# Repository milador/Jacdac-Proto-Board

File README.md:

# Jacdac-Proto-Board
A protoboard for Jacdac plug-and-play microcontrollers

The goal of this project ia to create a custom protoboard with built-in support for Jacdac plug-and-play for microcontrollers. This custom protoboard allows the makers to prototype their ideas for Jacdac ecosystem.

## Features

  1. Jacdac Connectors x 2
  2. (5 x 12) connection pins x 1
  3. (1 x 12) Power rails x 1
  4. [Footprint for 3.5mm Stereo Jack (SJ1-3513)](https://www.digikey.com/en/products/detail/cui-devices/SJ1-3513/738683) x 2
  5. 3-Pin headers for Jacdac connectors x 2
  6. 1-Pin headers for 3.5mm Stereo Jack x 2

## Hardware

### Printed Circuit Board Design Files

All the EAGLE PCB design files and gerber files are available and can be downloaded using the following link:

<a href="https://github.com/milador/Jacdac-Proto-Board/tree/main/Hardware/PCB/Eagle">EAGLE Design files</a>

<a href="https://github.com/milador/Jacdac-Proto-Board/blob/main/Hardware/PCB/Gerbers/Jacdac_Proto_Board.zip">Gerber files</a>

### 3D Model of the Printed Circuit Board Design

The 3D Model of protoboard is available in STL format for 3D printing before PCB fabrication and can be downloaded using the following link:

<a href="https://github.com/milador/Jacdac-Proto-Board/blob/main/Hardware/3D-Model/Jacdac_Proto_Board_3D_Model.stl">STL file</a>

## Images

Top View:

Bottom View:

3D Model Top View:

3D Model  Bottom View:

Fabricated PCBs:

## License 

### MIT License

Copyright (c) 2021 Milador

Permission is hereby granted, free of charge, to any person obtaining a copy of this software and associated documentation files (the "Software"), to deal in the Software without restriction, including without limitation the rights to use, copy, modify, merge, publish, distribute, sublicense, and/or sell copies of the Software, and to permit persons to whom the Software is furnished to do so, subject to the following conditions:

The above copyright notice and this permission notice shall be included in all copies or substantial portions of the Software.

THE SOFTWARE IS PROVIDED "AS IS", WITHOUT WARRANTY OF ANY KIND, EXPRESS OR IMPLIED, INCLUDING BUT NOT LIMITED TO THE WARRANTIES OF MERCHANTABILITY, FITNESS FOR A PARTICULAR PURPOSE AND NONINFRINGEMENT. IN NO EVENT SHALL THE AUTHORS OR COPYRIGHT HOLDERS BE LIABLE FOR ANY CLAIM, DAMAGES OR OTHER LIABILITY, WHETHER IN AN ACTION OF CONTRACT, TORT OR OTHERWISE, ARISING FROM, OUT OF OR IN CONNECTION WITH THE SOFTWARE OR THE USE OR OTHER DEALINGS IN THE SOFTWARE.

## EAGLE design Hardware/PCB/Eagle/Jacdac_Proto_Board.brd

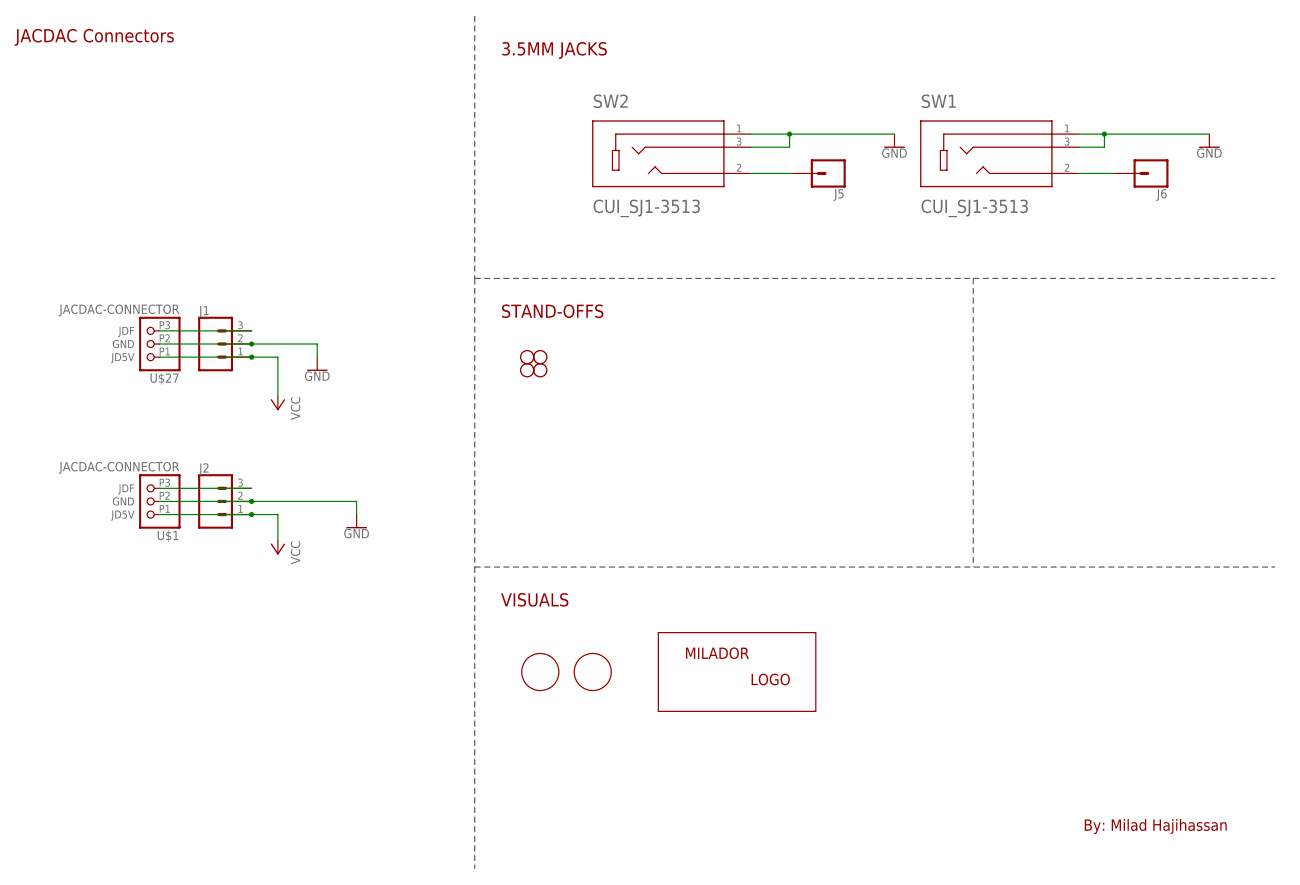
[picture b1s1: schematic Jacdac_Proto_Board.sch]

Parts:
H1, H2: STAND-OFF
J1, J2: CONNECTORS_CONN_03PTH; CONNECTORS_1X03
J5, J6: CONNECTORS_CONN_01PTH_NO_SILK_YES_STOP; CONNECTORS_1X01_NO_SILK
JP3, JP4: STAND-OFF
SW1, SW2: CUI_SJ1-3513
U$1, U$27: JACDAC-CONNECTOR
U$2: MILADOR-LOGO-; MILADOR_LOGO1
U$17: MILADOR-SWITCH-NAME-SW1; SWITCH-SW1
U$18: MILADOR-SWITCH-NAME-SW2; SWITCH-SW2

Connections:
GND: J1.2, J2.2, SW1.1, SW1.3, SW2.1, SW2.3, U$1.P2 (GND), U$27.P2 (GND)
unnamed: J6.1, SW1.2
unnamed: J5.1, SW2.2
unnamed: J1.3, U$27.P3 (JDF)
unnamed: J2.3, U$1.P3 (JDF)
VCC: J1.1, J2.1, U$1.P1 (JD5V), U$27.P1 (JD5V)

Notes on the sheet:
By: Milad Hajihassan
STAND-OFFS
VISUALS
3.5MM JACKS
JACDAC Connectors

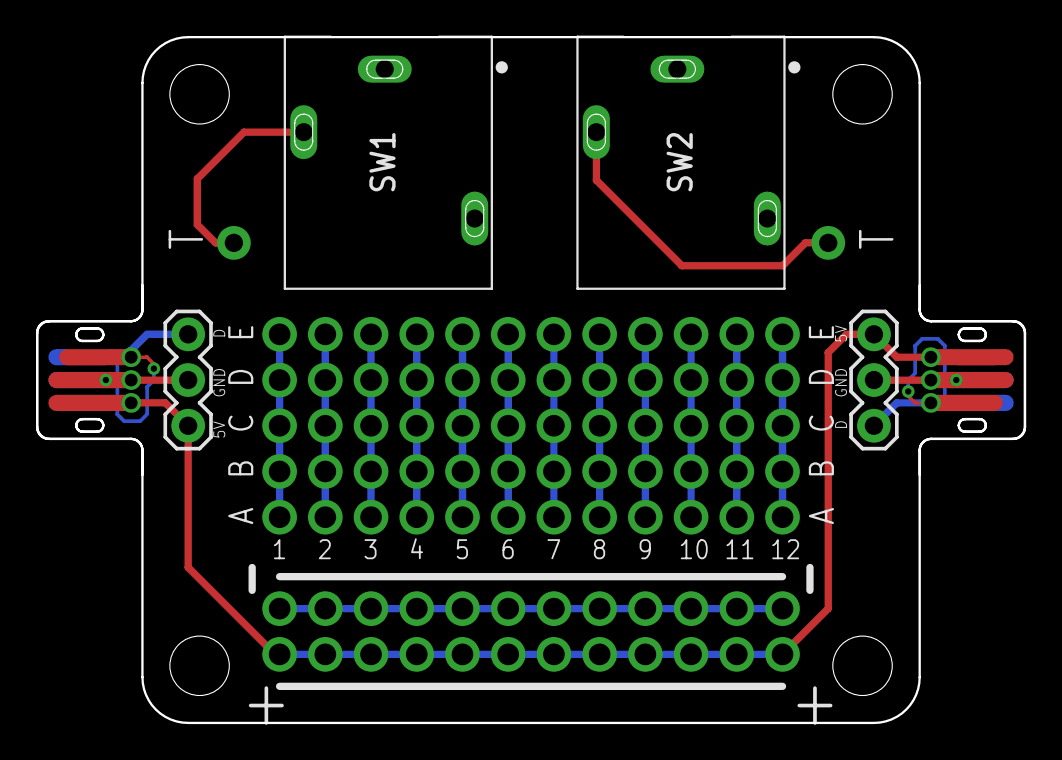
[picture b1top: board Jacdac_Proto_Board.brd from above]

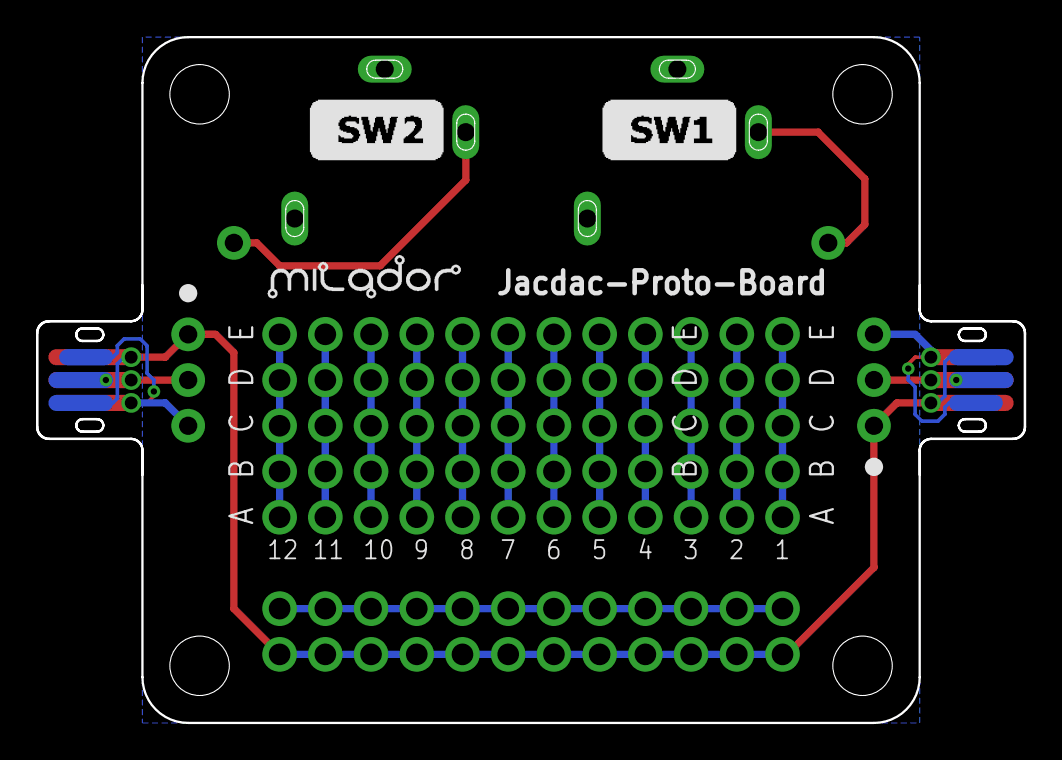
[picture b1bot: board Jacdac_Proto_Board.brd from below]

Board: 2 copper layers, 54.9 x 38.1 mm, 15 parts (3 on the bottom side), 6 nets.

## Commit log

2021-06-21 Added PCB design files
2021-06-21 Added images
2021-06-21 Added 3D Model STL file
2021-06-21 Updated readme file
2021-06-21 Updated readme file
    Updated the links
2021-06-21 Added library
2021-06-23 Updated PCB design files
2021-06-23 Updated images : Added title
2021-06-23 Updated STL file

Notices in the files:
parts and their libraries:
SparkFun-Hardware: Licensing: Creative Commons ShareAlike 4.0 International - https://creativecommons.org/licenses/by-sa/4.0
